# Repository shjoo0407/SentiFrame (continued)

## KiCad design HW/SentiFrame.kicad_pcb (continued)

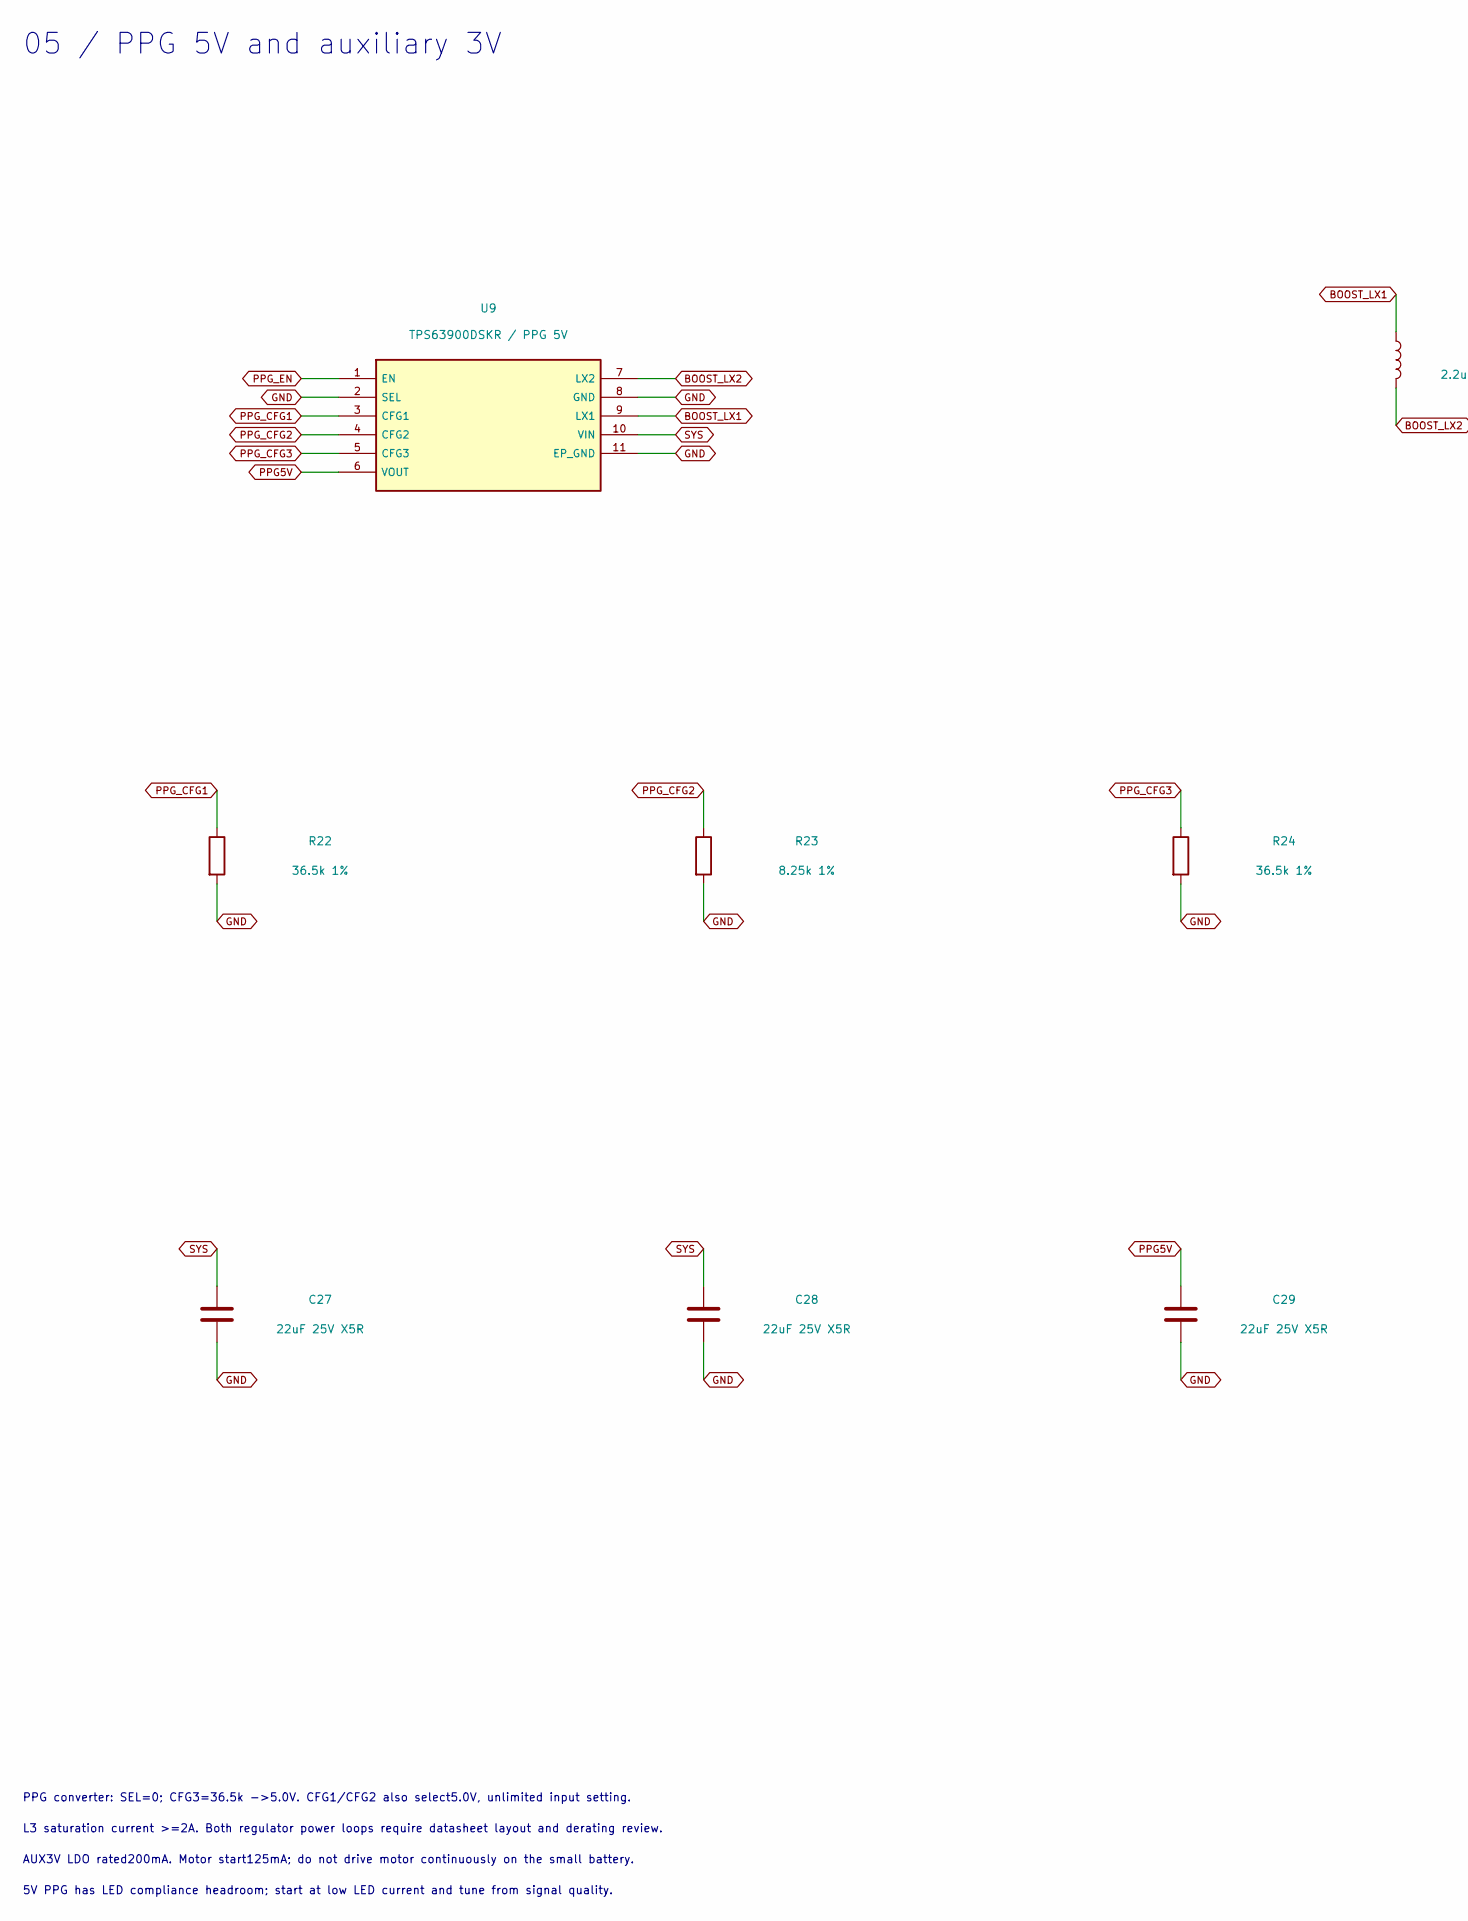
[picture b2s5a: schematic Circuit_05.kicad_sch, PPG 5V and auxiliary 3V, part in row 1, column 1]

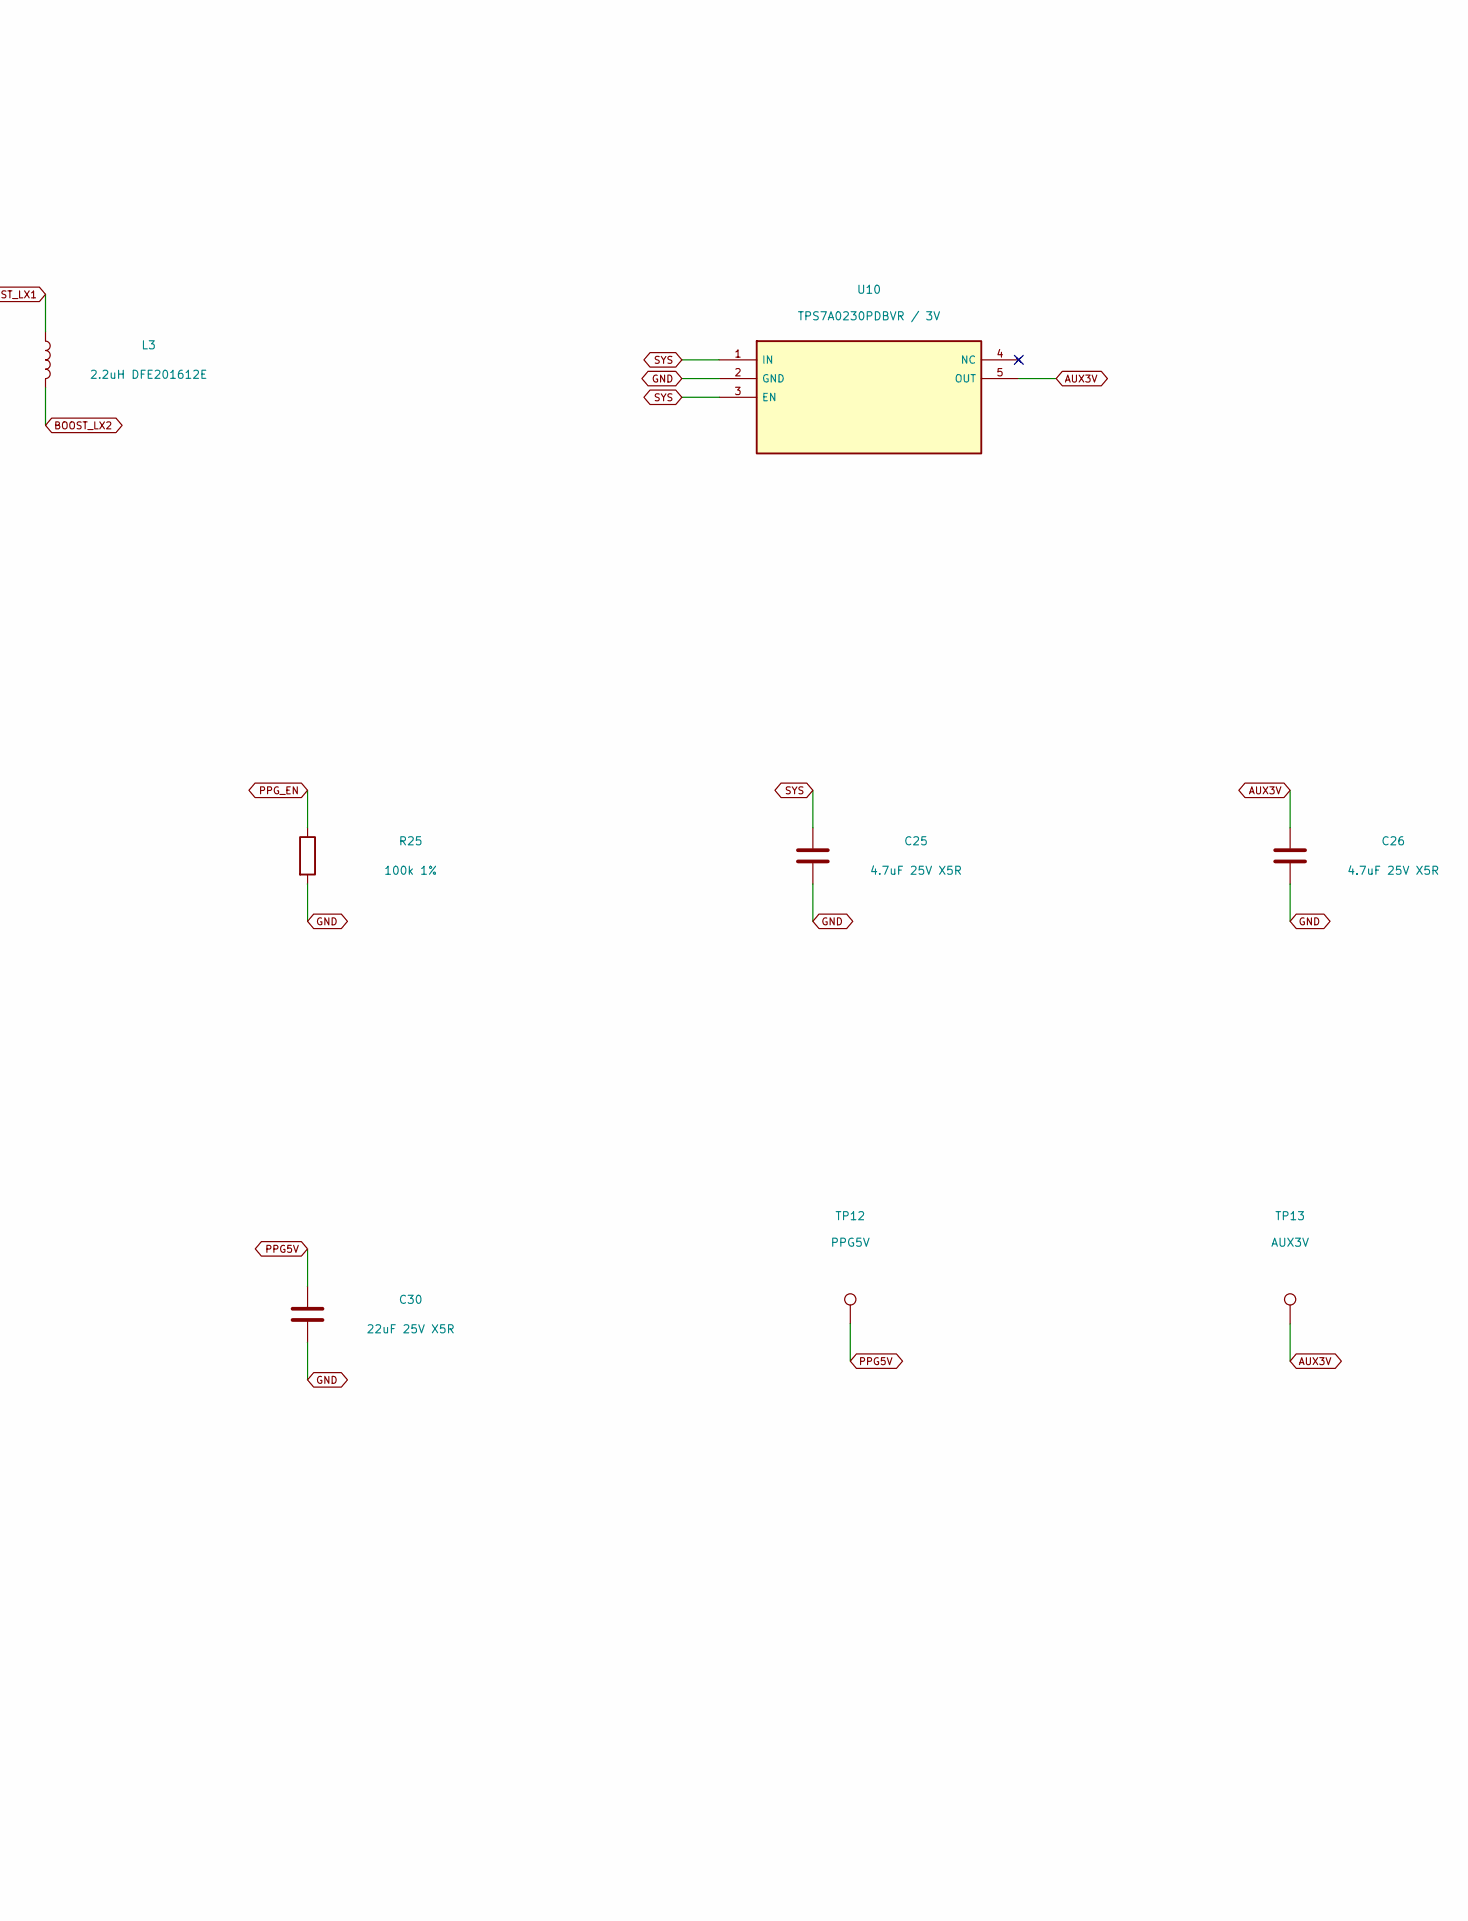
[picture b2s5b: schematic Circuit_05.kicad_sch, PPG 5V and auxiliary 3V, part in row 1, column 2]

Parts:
C25, C26: 4.7uF 25V X5R; C_0603_1608Metric; MPN C1608X5R1E475K080AC
C27, C28, C29, C30: 22uF 25V X5R; C_0805_2012Metric; MPN C2012X5R1E226M125AC
L3: 2.2uH DFE201612E; L_DFE201612E_DS; MPN DFE201612E-2R2M=P2
R22, R24: 36.5k 1%; R_0402_1005Metric; MPN RC0402FR-0736K5L
R23: 8.25k 1%; R_0402_1005Metric; MPN RC0402FR-078K25L
R25: 100k 1%; R_0402_1005Metric; MPN RC0402FR-07100KL
TP12: PPG5V; TestPoint_Pad_D1.0mm
TP13: AUX3V; TestPoint_Pad_D1.0mm
U9: TPS63900DSKR / PPG 5V; WSON-10-1EP_2.5x2.5mm_P0.5mm_EP1.2x2mm; MPN TPS63900DSKR
U10: TPS7A0230PDBVR / 3V; SOT-23-5; MPN TPS7A0230PDBVR

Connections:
AUX3V: C26.1, TP13.1, U10.5 (OUT); also elsewhere on the board
BOOST_LX1: L3.1, U9.9 (LX1)
BOOST_LX2: L3.2, U9.7 (LX2)
GND: C25.2, C26.2, C27.2, C28.2, C29.2, C30.2, R22.2, R23.2, R24.2, R25.2, U9.2 (SEL), U9.8 (GND), U9.11 (EP_GND), U10.2 (GND); also elsewhere on the board
PPG5V: C29.1, C30.1, TP12.1, U9.6 (VOUT); also elsewhere on the board
PPG_CFG1: R22.1, U9.3 (CFG1)
PPG_CFG2: R23.1, U9.4 (CFG2)
PPG_CFG3: R24.1, U9.5 (CFG3)
PPG_EN: R25.1, U9.1 (EN); also elsewhere on the board
SYS: C25.1, C27.1, C28.1, U9.10 (VIN), U10.1 (IN), U10.3 (EN); also elsewhere on the board

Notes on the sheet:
05 / PPG 5V and auxiliary 3V
PPG converter: SEL=0; CFG3=36.5k ->5.0V. CFG1/CFG2 also select5.0V, unlimited input setting.
L3 saturation current >=2A. Both regulator power loops require datasheet layout and derating review.
AUX3V LDO rated200mA. Motor start125mA; do not drive motor continuously on the small battery.
5V PPG has LED compliance headroom; start at low LED current and tune from signal quality.

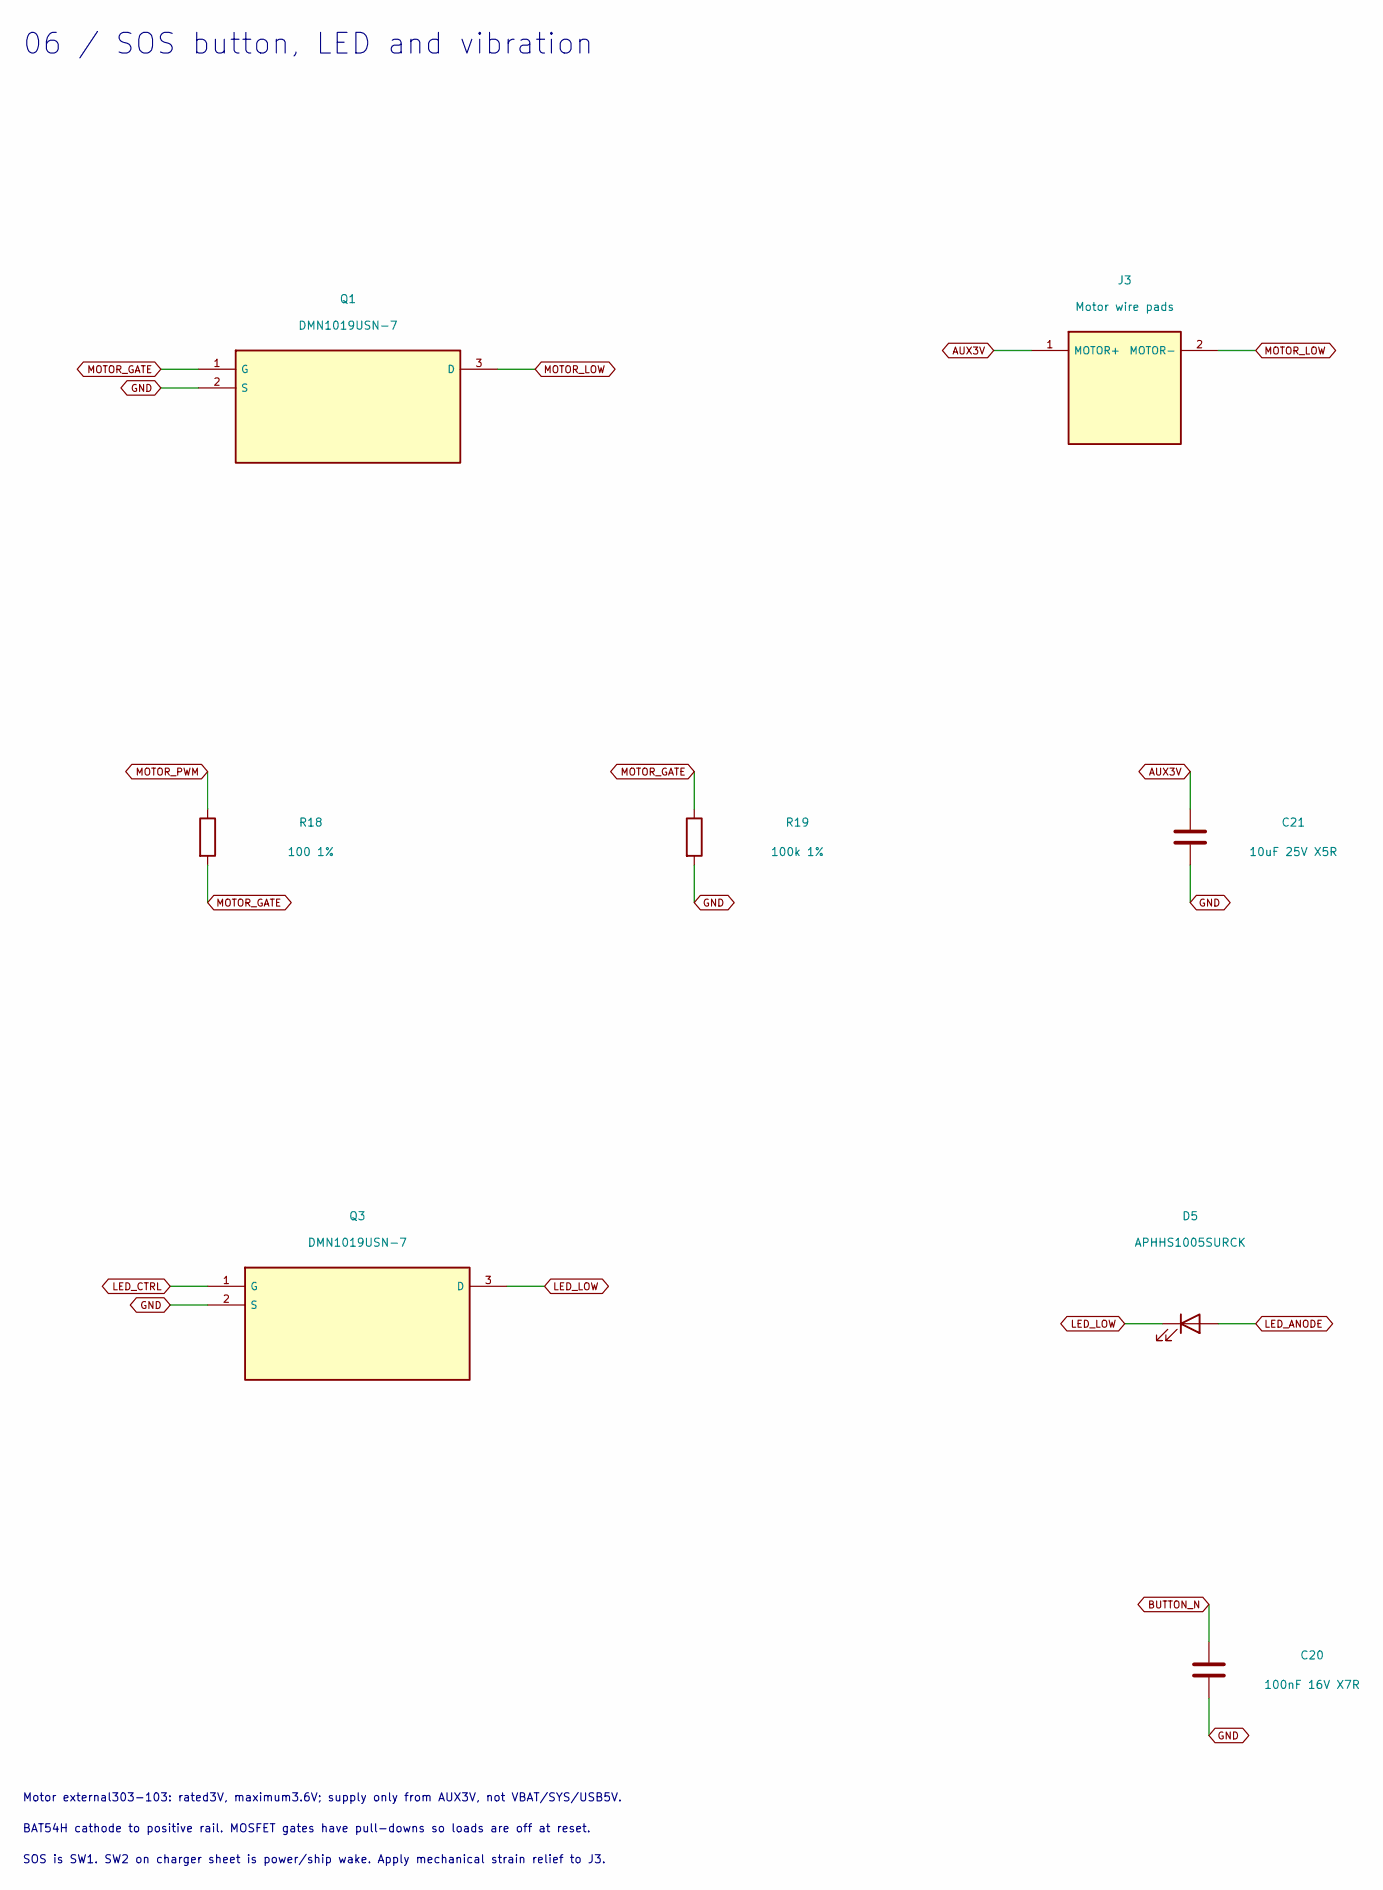
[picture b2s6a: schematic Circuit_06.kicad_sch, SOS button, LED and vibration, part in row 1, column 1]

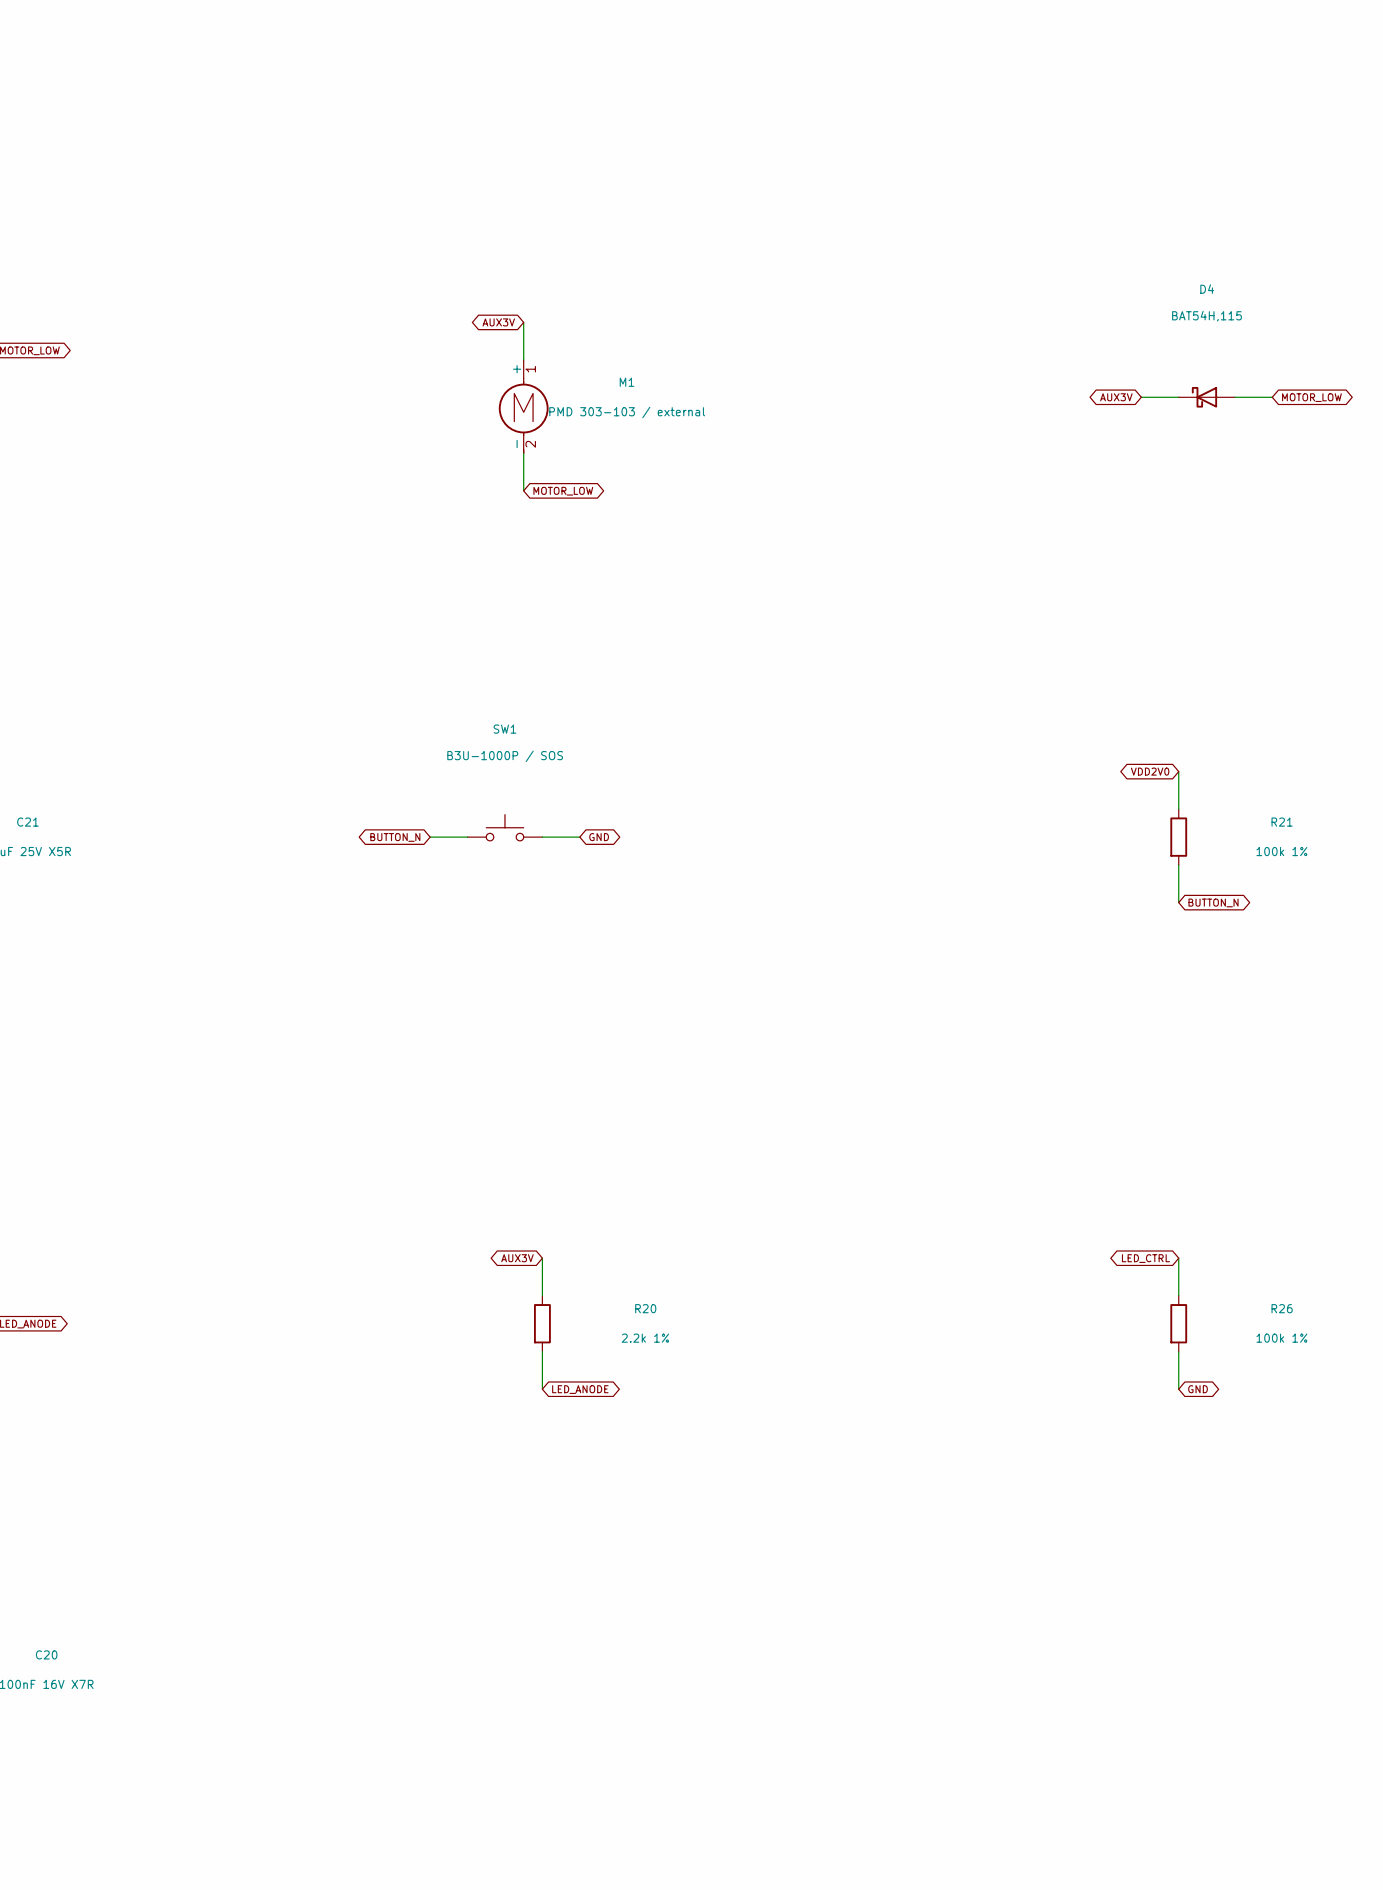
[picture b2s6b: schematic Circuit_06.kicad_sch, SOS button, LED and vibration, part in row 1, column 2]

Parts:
C20: 100nF 16V X7R; C_0402_1005Metric; MPN C1005X7R1C104K050BC
C21: 10uF 25V X5R; C_0805_2012Metric; MPN C2012X5R1E106K125AB
D4: BAT54H,115; D_SOD-123F; MPN BAT54H,115
D5: APHHS1005SURCK; LED_0402_1005Metric; MPN APHHS1005SURCK
J3: Motor wire pads; Motor_Wire_Pads_2P
M1: PMD 303-103 / external; MPN 303-103
Q1, Q3: DMN1019USN-7; SC-59; MPN DMN1019USN-7
R18: 100 1%; R_0402_1005Metric; MPN RC0402FR-07100RL
R19, R21, R26: 100k 1%; R_0402_1005Metric; MPN RC0402FR-07100KL
R20: 2.2k 1%; R_0402_1005Metric; MPN RC0402FR-072K2L
SW1: B3U-1000P / SOS; SW_SPST_B3U-1000P; MPN B3U-1000P

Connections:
AUX3V: C21.1, D4.1 (K), J3.1 (MOTOR+), M1.1 (+), R20.1; also elsewhere on the board
BUTTON_N: C20.1, R21.2, SW1.1; also elsewhere on the board
GND: C20.2, C21.2, Q1.2 (S), Q3.2 (S), R19.2, R26.2, SW1.2; also elsewhere on the board
LED_ANODE: D5.2 (A), R20.2
LED_CTRL: Q3.1 (G), R26.1; also elsewhere on the board
LED_LOW: D5.1 (K), Q3.3 (D)
MOTOR_GATE: Q1.1 (G), R18.2, R19.1
MOTOR_LOW: D4.2 (A), J3.2 (MOTOR-), M1.2 (-), Q1.3 (D)
MOTOR_PWM: R18.1; also elsewhere on the board
VDD2V0: R21.1; also elsewhere on the board

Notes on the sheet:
06 / SOS button, LED and vibration
Motor external303-103: rated3V, maximum3.6V; supply only from AUX3V, not VBAT/SYS/USB5V.
BAT54H cathode to positive rail. MOSFET gates have pull-downs so loads are off at reset.
SOS is SW1. SW2 on charger sheet is power/ship wake. Apply mechanical strain relief to J3.

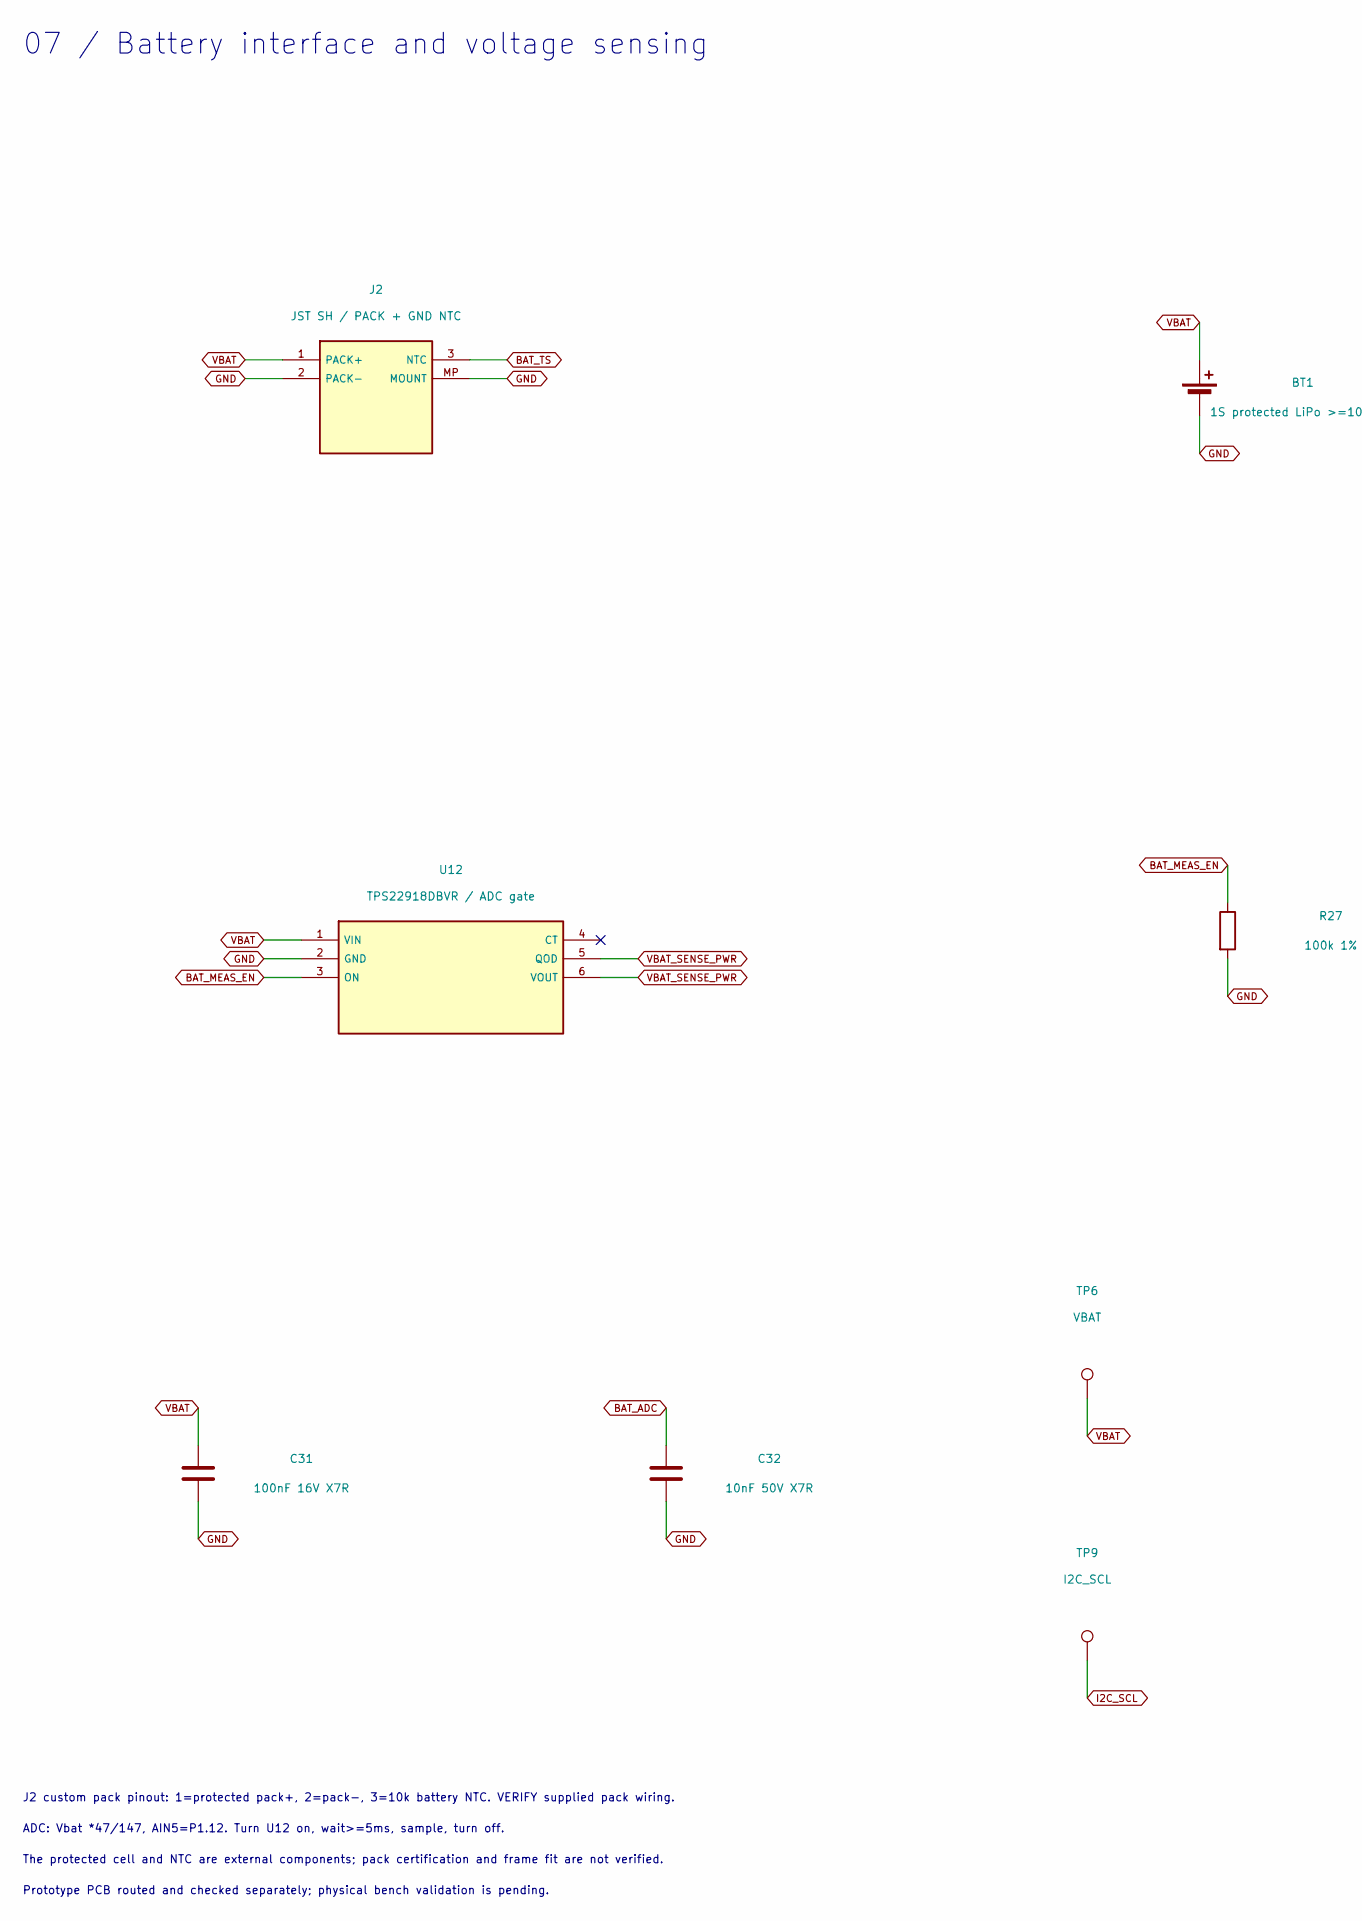
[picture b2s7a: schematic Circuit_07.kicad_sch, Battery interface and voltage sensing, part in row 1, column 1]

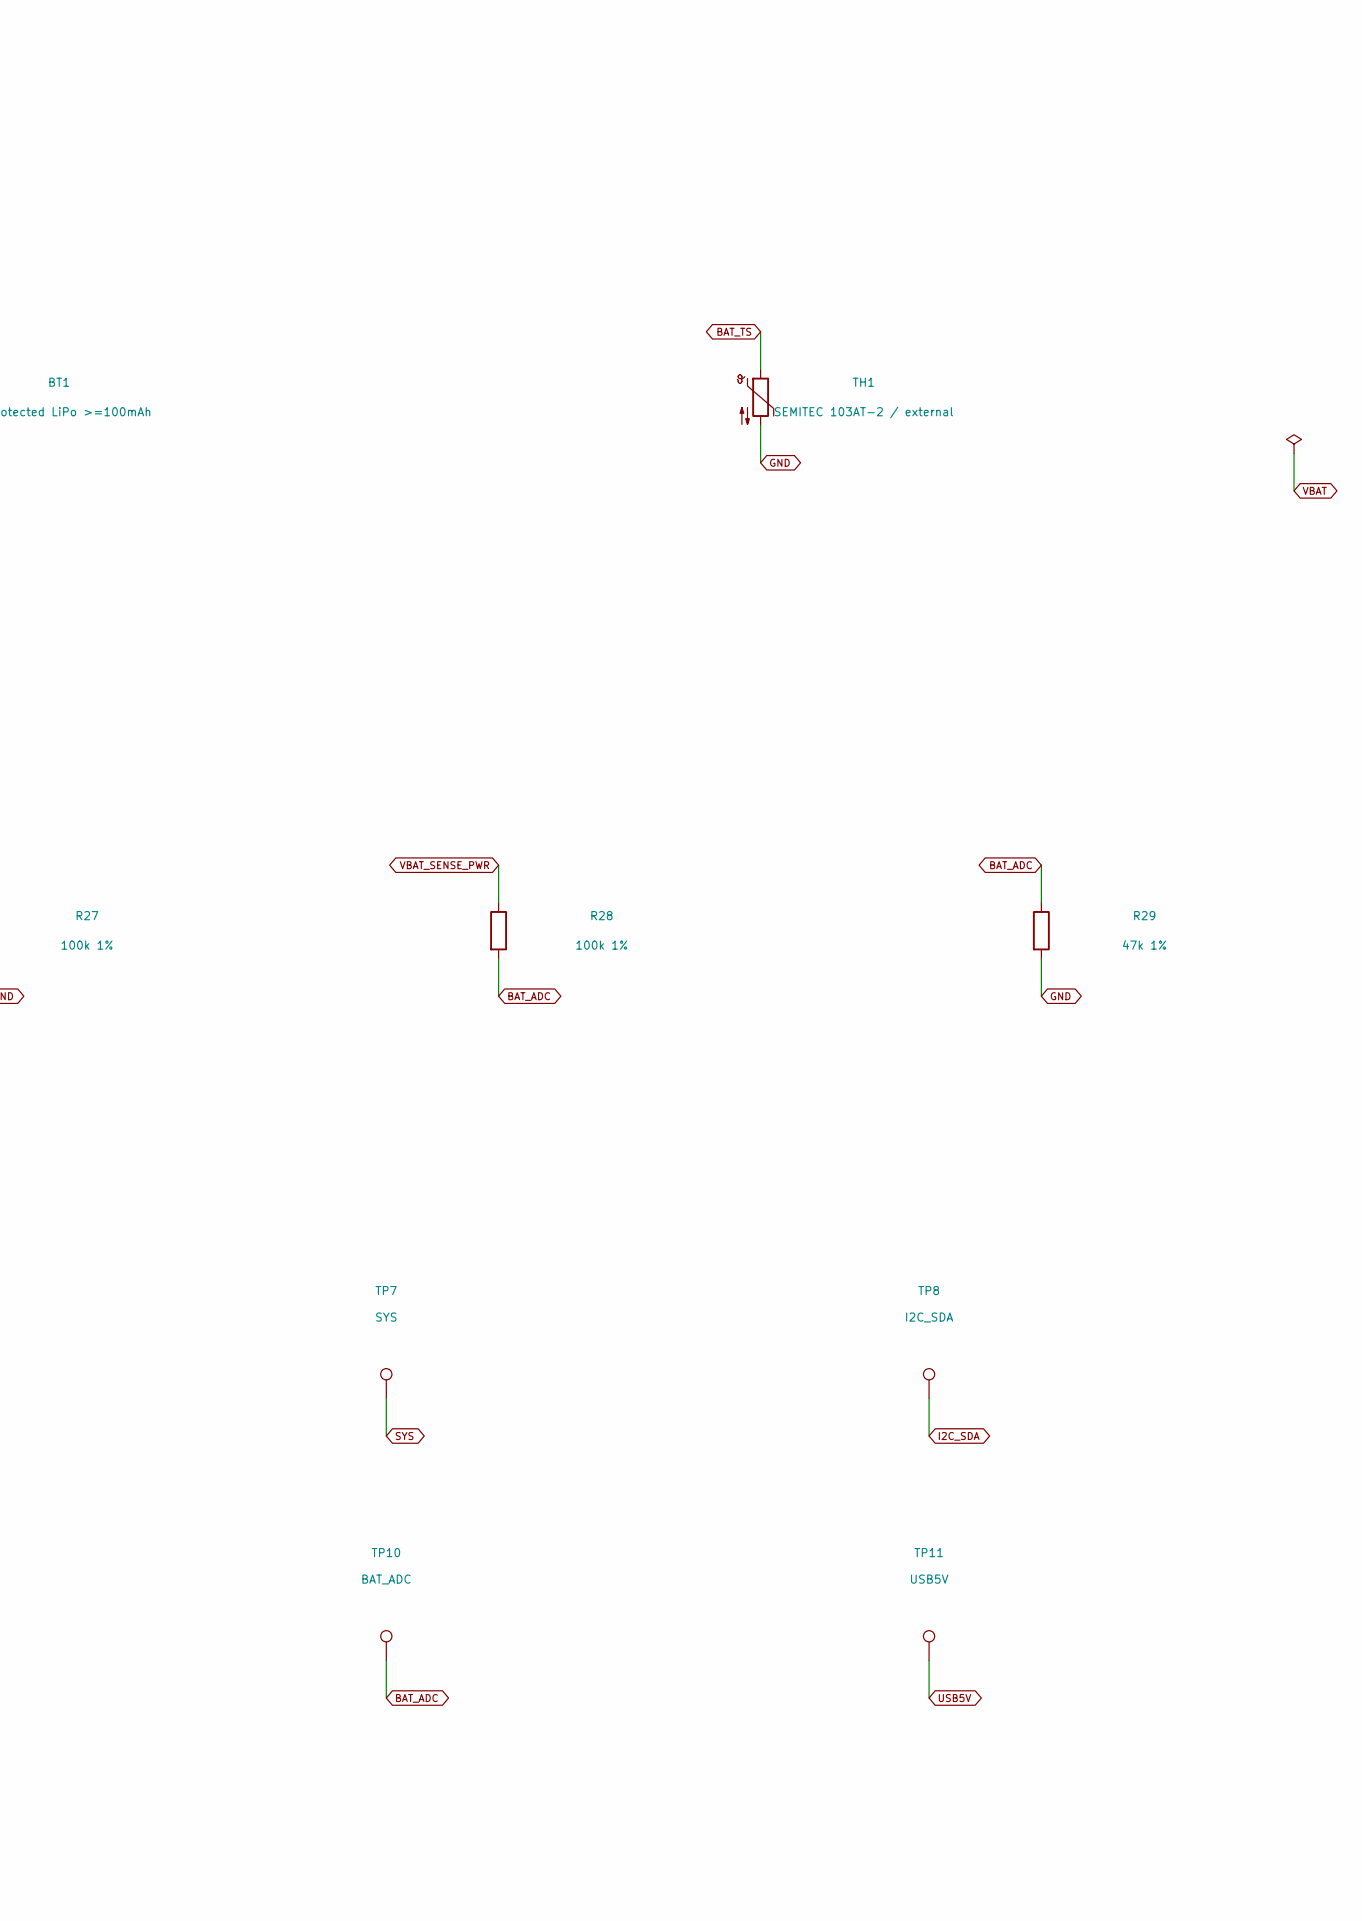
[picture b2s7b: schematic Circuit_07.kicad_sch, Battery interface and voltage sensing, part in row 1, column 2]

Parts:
BT1: 1S protected LiPo >=100mAh; MPN SF-PACK-001 interface specification
C31: 100nF 16V X7R; C_0402_1005Metric; MPN C1005X7R1C104K050BC
C32: 10nF 50V X7R; C_0402_1005Metric; MPN C1005X7R1H103K050BB
J2: JST SH / PACK + GND NTC; JST_SH_SM03B-SRSS-TB_1x03-1MP_P1.00mm_Horizontal; MPN SM03B-SRSS-TB
R27, R28: 100k 1%; R_0402_1005Metric; MPN RC0402FR-07100KL
R29: 47k 1%; R_0402_1005Metric; MPN RC0402FR-0747KL
TH1: SEMITEC 103AT-2 / external; MPN 103AT-2
TP6: VBAT; TestPoint_Pad_D1.0mm
TP7: SYS; TestPoint_Pad_D1.0mm
TP8: I2C_SDA; TestPoint_Pad_D1.0mm
TP9: I2C_SCL; TestPoint_Pad_D1.0mm
TP10: BAT_ADC; TestPoint_Pad_D1.0mm
TP11: USB5V; TestPoint_Pad_D1.0mm
U12: TPS22918DBVR / ADC gate; SOT-23-6; MPN TPS22918DBVR

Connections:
BAT_ADC: C32.1, R28.2, R29.1, TP10.1; also elsewhere on the board
BAT_MEAS_EN: R27.1, U12.3 (ON); also elsewhere on the board
BAT_TS: J2.3 (NTC), TH1.1; also elsewhere on the board
GND: BT1.2 (-), C31.2, C32.2, J2.2 (PACK-), J2.MP (MOUNT), R27.2, R29.2, TH1.2, U12.2 (GND); also elsewhere on the board
I2C_SCL: TP9.1; also elsewhere on the board
I2C_SDA: TP8.1; also elsewhere on the board
SYS: TP7.1; also elsewhere on the board
USB5V: TP11.1; also elsewhere on the board
VBAT: BT1.1 (+), C31.1, J2.1 (PACK+), TP6.1, U12.1 (VIN); also elsewhere on the board
VBAT_SENSE_PWR: R28.1, U12.5 (QOD), U12.6 (VOUT)

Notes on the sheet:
07 / Battery interface and voltage sensing
J2 custom pack pinout: 1=protected pack+, 2=pack-, 3=10k battery NTC. VERIFY supplied pack wiring.
ADC: Vbat *47/147, AIN5=P1.12. Turn U12 on, wait>=5ms, sample, turn off.
The protected cell and NTC are external components; pack certification and frame fit are not verified.
Prototype PCB routed and checked separately; physical bench validation is pending.
